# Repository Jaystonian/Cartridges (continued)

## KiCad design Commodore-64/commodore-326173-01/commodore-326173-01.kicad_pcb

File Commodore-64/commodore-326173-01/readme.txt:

Improved Commodore 326173-01 Cartridge

* Reset circuitry may be omitted completely

J1-J5 as expected for original Commodore PCB
  J1=~ROML~  J2=~ROMH~  J3=~GAME~  J4=~EXROM~  J5=Connect ~IO2~ to ~EXROM~

**U1 CONFIG**
U1=2364
  JP1-JP5 close arrowed "1" side
  JP6 close (R3,R4,R5 not needed)
  J7 not needed

U1=2764
  JP1-JP2 close "3" side
  JP3-JP5 close "1" side
  Install R4, R5
  J7 not needed

U1=27128 (two 8KB roms)
  JP1-JP3 close "3" side
  JP4-JP5 close "1" side
  Install R3, R4, R5
  J7 - SPST switch between Pin 1 & 2 (GND and SA13)

U1=27256 (four 8KB roms)
  JP1-JP4 close "3" side
  JP5 close "1" side
  Install R3, R4, R5

U1=27512 (eight 8KB roms)
  JP1-JP5 close "3" side
  Install R3, R4, R5

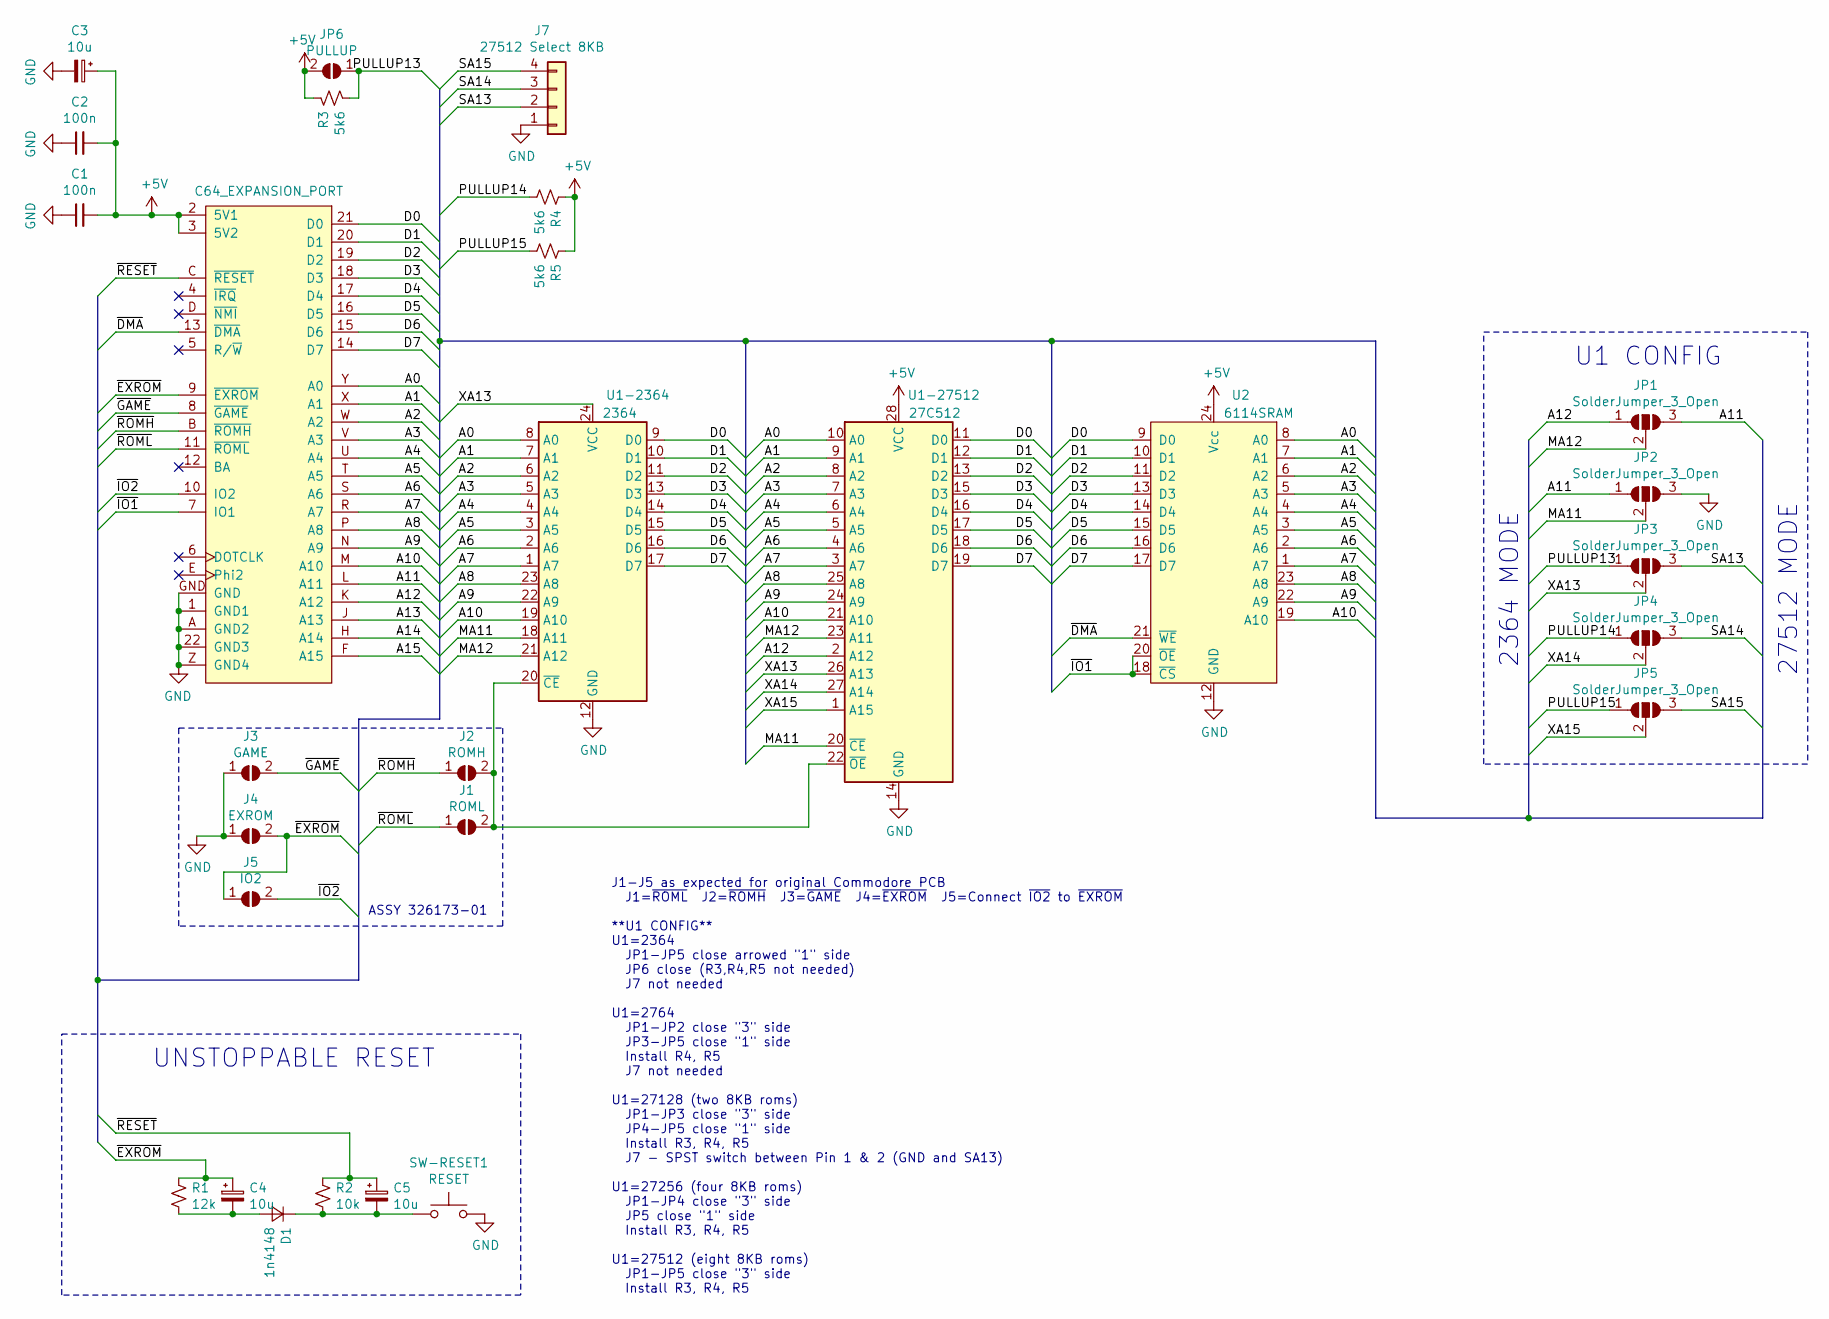
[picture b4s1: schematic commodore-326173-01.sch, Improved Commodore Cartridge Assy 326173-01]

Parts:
C1, C2: 100n; C_0805_2012Metric_Pad1.15x1.40mm_HandSolder
C3, C4, C5: 10u; CP_Radial_D5.0mm_P2.50mm
D1: 1n4148; D_DO-34_SOD68_P7.62mm_Horizontal
J1: ROML; SolderJumper-2_P1.3mm_Open_RoundedPad1.0x1.5mm
J2: ROMH; SolderJumper-2_P1.3mm_Open_RoundedPad1.0x1.5mm
J3: GAME; SolderJumper-2_P1.3mm_Open_RoundedPad1.0x1.5mm
J4: EXROM; SolderJumper-2_P1.3mm_Open_RoundedPad1.0x1.5mm
J5: IO2; SolderJumper-2_P1.3mm_Open_RoundedPad1.0x1.5mm
J7: 27512 Select 8KB; PinHeader_1x04_P2.54mm_Vertical
JP1, JP2, JP3, JP4, JP5: SolderJumper_3_Open; SolderJumper-3_P1.3mm_Open_RoundedPad1.0x1.5mm
JP6: PULLUP; SolderJumper-2_P1.3mm_Open_RoundedPad1.0x1.5mm
R1: 12k; R_0805_2012Metric_Pad1.15x1.40mm_HandSolder
R2: 10k; R_0805_2012Metric_Pad1.15x1.40mm_HandSolder
R3, R4, R5: 5k6; R_0805_2012Metric_Pad1.15x1.40mm_HandSolder
SW-RESET1: RESET; SW_PUSH_6mm_H8mm
U1-2364: 2364; DIP-24_W15.24mm
U1-27512: 27C512; DIP-28_W15.24mm
U2: 6114SRAM; DIP-24_W15.24mm
X1: C64_EXPANSION_PORT; C64_EXPANSION_CARD_68mm

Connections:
+5V: C1.2, C2.2, C3.1, JP6.2 (B), R3.1, R4.1, R5.1, U1-27512.28 (VCC), U2.24 (Vcc), X1.2 (5V1), X1.3 (5V2)
/A0: U1-2364.8 (A0), U1-27512.10 (A0), U2.8 (A0), X1.Y (A0)
/A1: U1-2364.7 (A1), U1-27512.9 (A1), U2.7 (A1), X1.X (A1)
/A2: U1-2364.6 (A2), U1-27512.8 (A2), U2.6 (A2), X1.W (A2)
/A3: U1-2364.5 (A3), U1-27512.7 (A3), U2.5 (A3), X1.V (A3)
/A4: U1-2364.4 (A4), U1-27512.6 (A4), U2.4 (A4), X1.U (A4)
/A5: U1-2364.3 (A5), U1-27512.5 (A5), U2.3 (A5), X1.T (A5)
/A6: U1-2364.2 (A6), U1-27512.4 (A6), U2.2 (A6), X1.S (A6)
/A7: U1-2364.1 (A7), U1-27512.3 (A7), U2.1 (A7), X1.R (A7)
/A8: U1-2364.23 (A8), U1-27512.25 (A8), U2.23 (A8), X1.P (A8)
/A9: U1-2364.22 (A9), U1-27512.24 (A9), U2.22 (A9), X1.N (A9)
/A10: U1-2364.19 (A10), U1-27512.21 (A10), U2.19 (A10), X1.M (A10)
/A11: JP1.3 (B), JP2.1 (A), X1.L (A11)
/A12: JP1.1 (A), U1-27512.2 (A12), X1.K (A12)
/A13: X1.J (A13)
/A14: X1.H (A14)
/A15: X1.F (A15)
/D0: U1-2364.9 (D0), U1-27512.11 (D0), U2.9 (D0), X1.21 (D0)
/D1: U1-2364.10 (D1), U1-27512.12 (D1), U2.10 (D1), X1.20 (D1)
/D2: U1-2364.11 (D2), U1-27512.13 (D2), U2.11 (D2), X1.19 (D2)
/D3: U1-2364.13 (D3), U1-27512.15 (D3), U2.13 (D3), X1.18 (D3)
/D4: U1-2364.14 (D4), U1-27512.16 (D4), U2.14 (D4), X1.17 (D4)
/D5: U1-2364.15 (D5), U1-27512.17 (D5), U2.15 (D5), X1.16 (D5)
/D6: U1-2364.16 (D6), U1-27512.18 (D6), U2.16 (D6), X1.15 (D6)
/D7: U1-2364.17 (D7), U1-27512.19 (D7), U2.17 (D7), X1.14 (D7)
/MA11: JP2.2 (C), U1-2364.18 (A11), U1-27512.20 (~CE)
/MA12: JP1.2 (C), U1-2364.21 (A12), U1-27512.23 (A11)
/PULLUP13: JP3.1 (A), JP6.1 (A), R3.2
/PULLUP14: JP4.1 (A), R4.2
/PULLUP15: JP5.1 (A), R5.2
/SA13: J7.2, JP3.3 (B)
/SA14: J7.3, JP4.3 (B)
/SA15: J7.4, JP5.3 (B)
/XA13: JP3.2 (C), U1-2364.24 (VCC), U1-27512.26 (A13)
/XA14: JP4.2 (C), U1-27512.27 (A14)
/XA15: JP5.2 (C), U1-27512.1 (A15)
/~DMA: U2.21 (~WE), X1.13 (~DMA~)
/~EXROM: C4.1, J4.2 (B), J5.1 (A), R1.2, X1.9 (~EXROM~)
/~GAME: J3.2 (B), X1.8 (~GAME~)
/~IO1: U2.18 (~CS), U2.20 (~OE), X1.7 (IO1)
/~IO2: J5.2 (B), X1.10 (IO2)
/~RESET: C5.1, R2.1, X1.C (~RESET~)
/~ROMH: J2.1 (A), X1.B (~ROMH~)
/~ROML: J1.1 (A), X1.11 (~ROML~)
GND: C1.1, C2.1, C3.2, J3.1 (A), J4.1 (A), J7.1, JP2.3 (B), SW-RESET1.2, U1-2364.12 (GND), U1-27512.14 (GND), U2.12 (GND), X1.1 (GND1), X1.22 (GND3), X1.A (GND2), X1.GND, X1.Z (GND4)
unnamed: C4.2, D1.2 (A), R1.1
unnamed: C5.2, D1.1 (K), R2.2, SW-RESET1.1
unnamed: J1.2 (B), J2.2 (B), U1-2364.20 (~CE), U1-27512.22 (~OE)

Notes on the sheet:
UNSTOPPABLE RESET
27512 MODE
2364 MODE
U1 CONFIG
ASSY 326173-01
J1-J5 as expected for original Commodore PCB J1=~ROML~ J2=~ROMH~ J3=~GAME~ J4=~EXROM~ J5=Connect ~IO2~ to ~EXROM~ **U1 CONFIG** U1=2364 JP1-JP5 close arrowed "1" side JP6 close (R3,R4,R5 not needed) J7 not needed U1=2764 JP1-JP2 close "3" side JP3-JP5 close "1" side Install R4, R5 J7 not needed U1=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

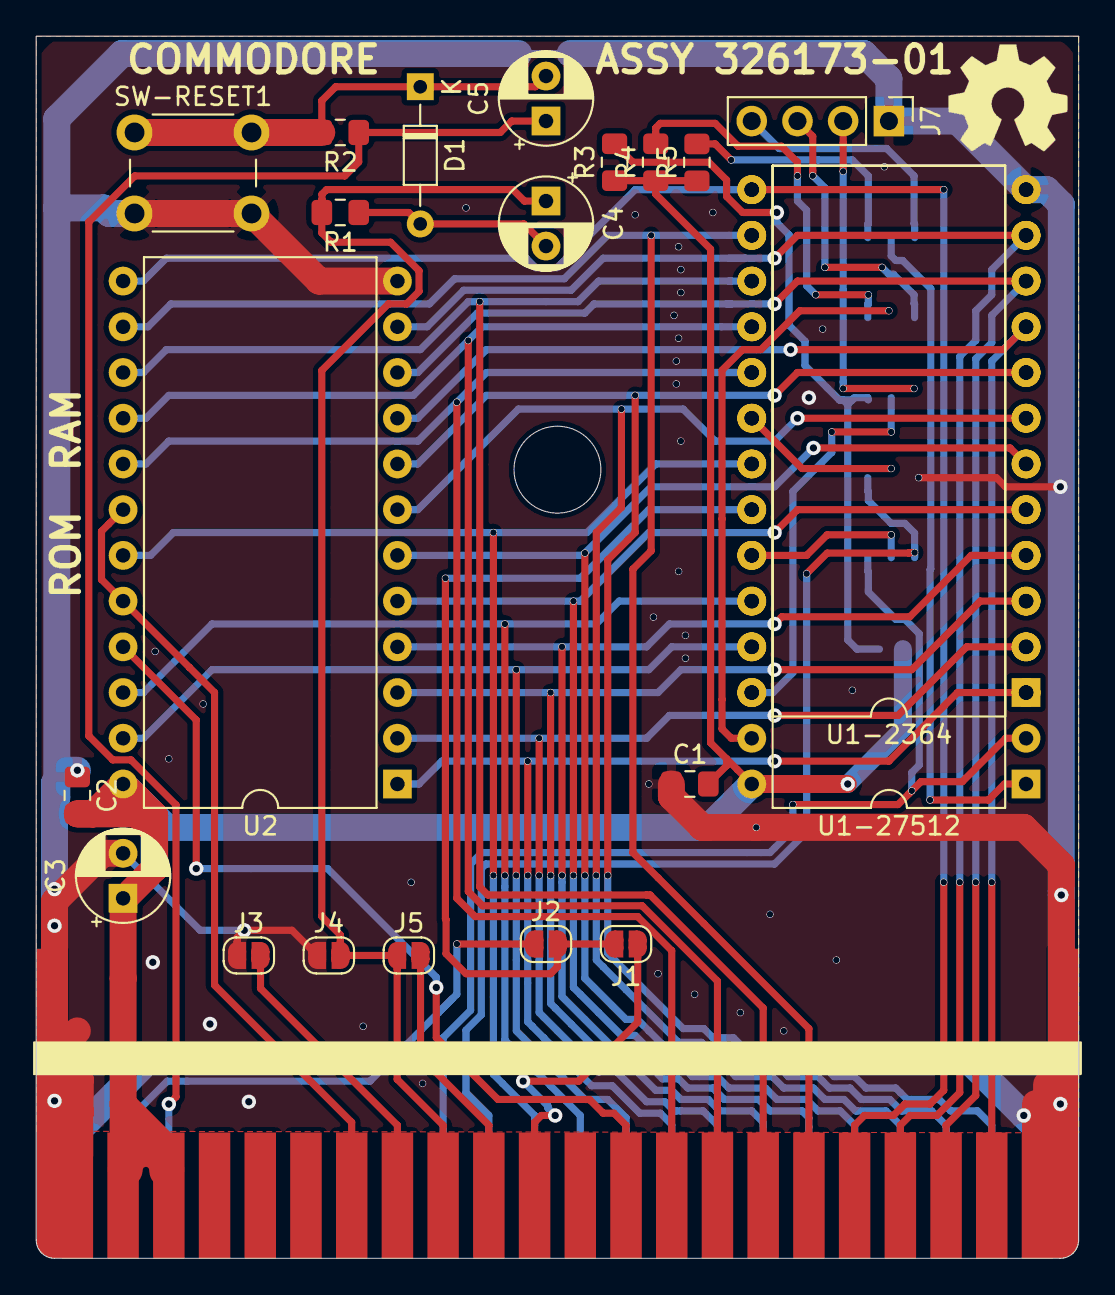
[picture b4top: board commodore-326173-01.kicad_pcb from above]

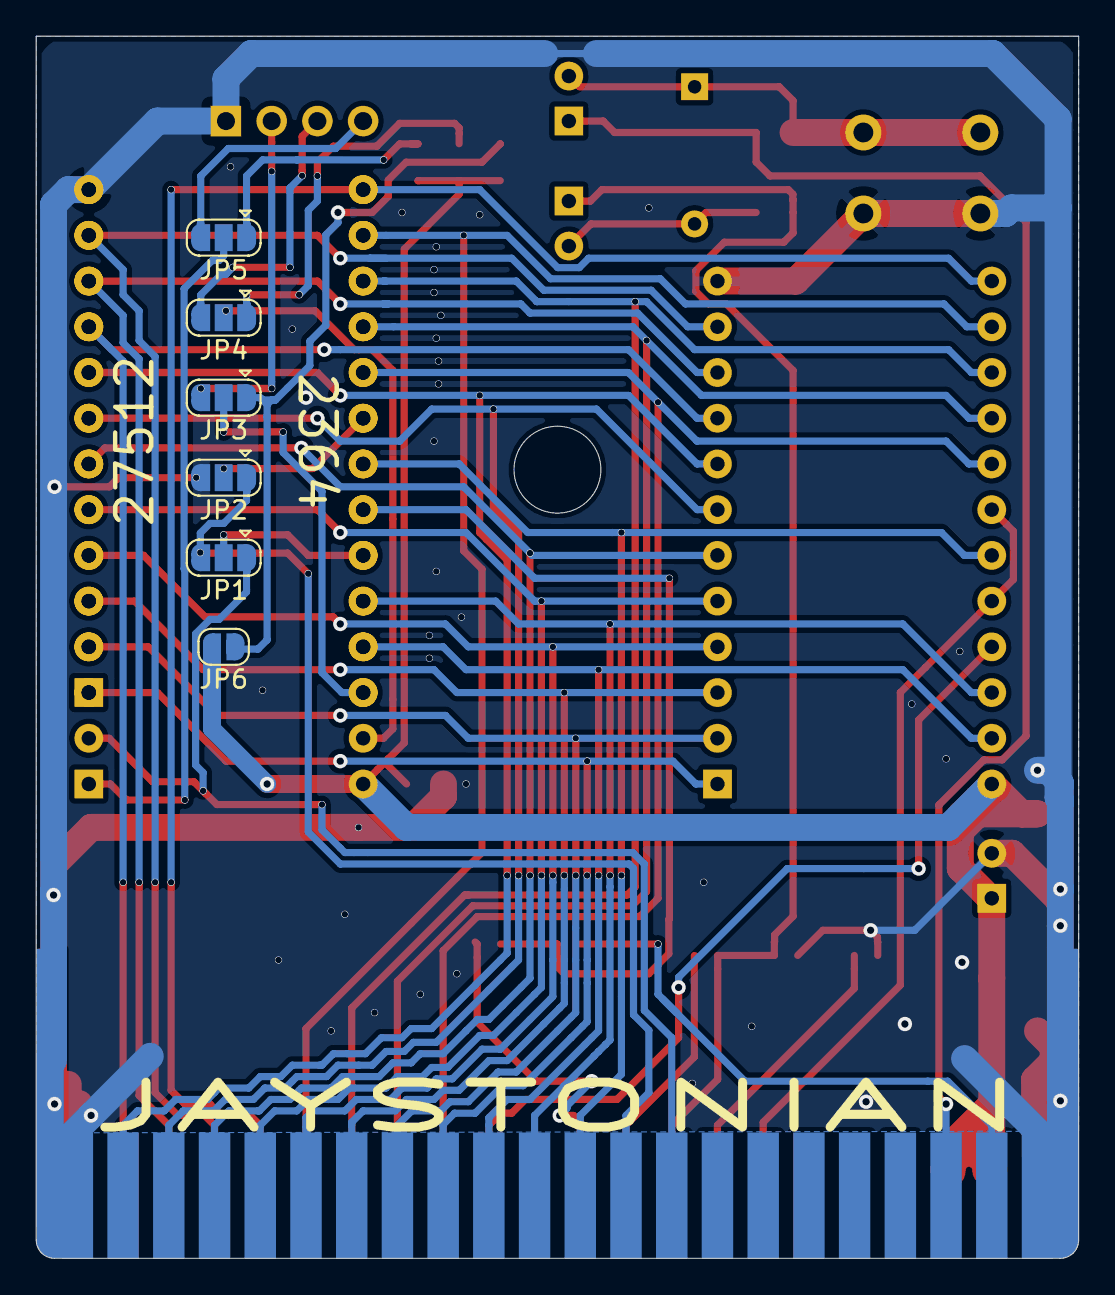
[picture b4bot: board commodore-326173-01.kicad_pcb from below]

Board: 2 copper layers, 57.9 x 67.9 mm, 28 parts (6 on the bottom side), 45 nets.

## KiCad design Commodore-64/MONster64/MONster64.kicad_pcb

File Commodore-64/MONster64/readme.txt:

MONster64 -- An STM32 Development Board for Commodore C64 & C128 Expansion Port

* Effectively an upgraded version of "Kung Fu Flash"

* fixes the PAL-only problem with KFF, due to jumper choice of DOTCLK or 
    standard 8MHz clock.  Internal PLL set to 468Mhz @ 8.000 MHz OSC_IN,
    which puts it close to 480MHz for NTSC and ~460MHz for PAL.

* may be installed with most other ARM-based code, such as BackBit, with light
    changes to GPIO.

* can be programmed with ST-LINK V2 or V3. I was unsuccessful connecting 
    a "blue pill" STM32F103 programmed to be an ST-LINK.

Contains an ARM Cortex M7 microcontroller, 22 exposed GPIO, 256MB Flash RAM, 
MicroSD card, MicroUSB -- all on a 2-LAYER PCB!

Also contains an expansion header for 10/100base-T networking or other 
high-speed interfacing such as video/sound.

Please see https://github.com/KimJorgensen/KungFuFlash for more information.

This project started when I took notice of KFF and started looking at STM32
schematics for all kinds of projects.  Then I decided I wanted an M7 based
card and not just an M4, and also on 2-layer PCB.

===============================================================================

2020-09-10: First status update. Beginning to port KFF code into CubeIDE.
  
    * Device is built, power domains are working, clock is working.

    * I can connect a MicroUSB cable to my computer, registers as a DFU, which
    can then be accessed by STM32 Cube Programmer via USB.
    
    * I can connect the ST-LINK V2 (SWDIO, SWCLK, GND, 5v, boot0 to link's 3v3)
    but it would not connect until I also connected 3v3 between the devices, 
    raising the target voltage reported in Cube Programmer from 3.17v to 3.20v.

    * I have updated the gerbers with small changes, I do not expect any further
    changes, device otherwise has passed basic tests.
===============================================================================

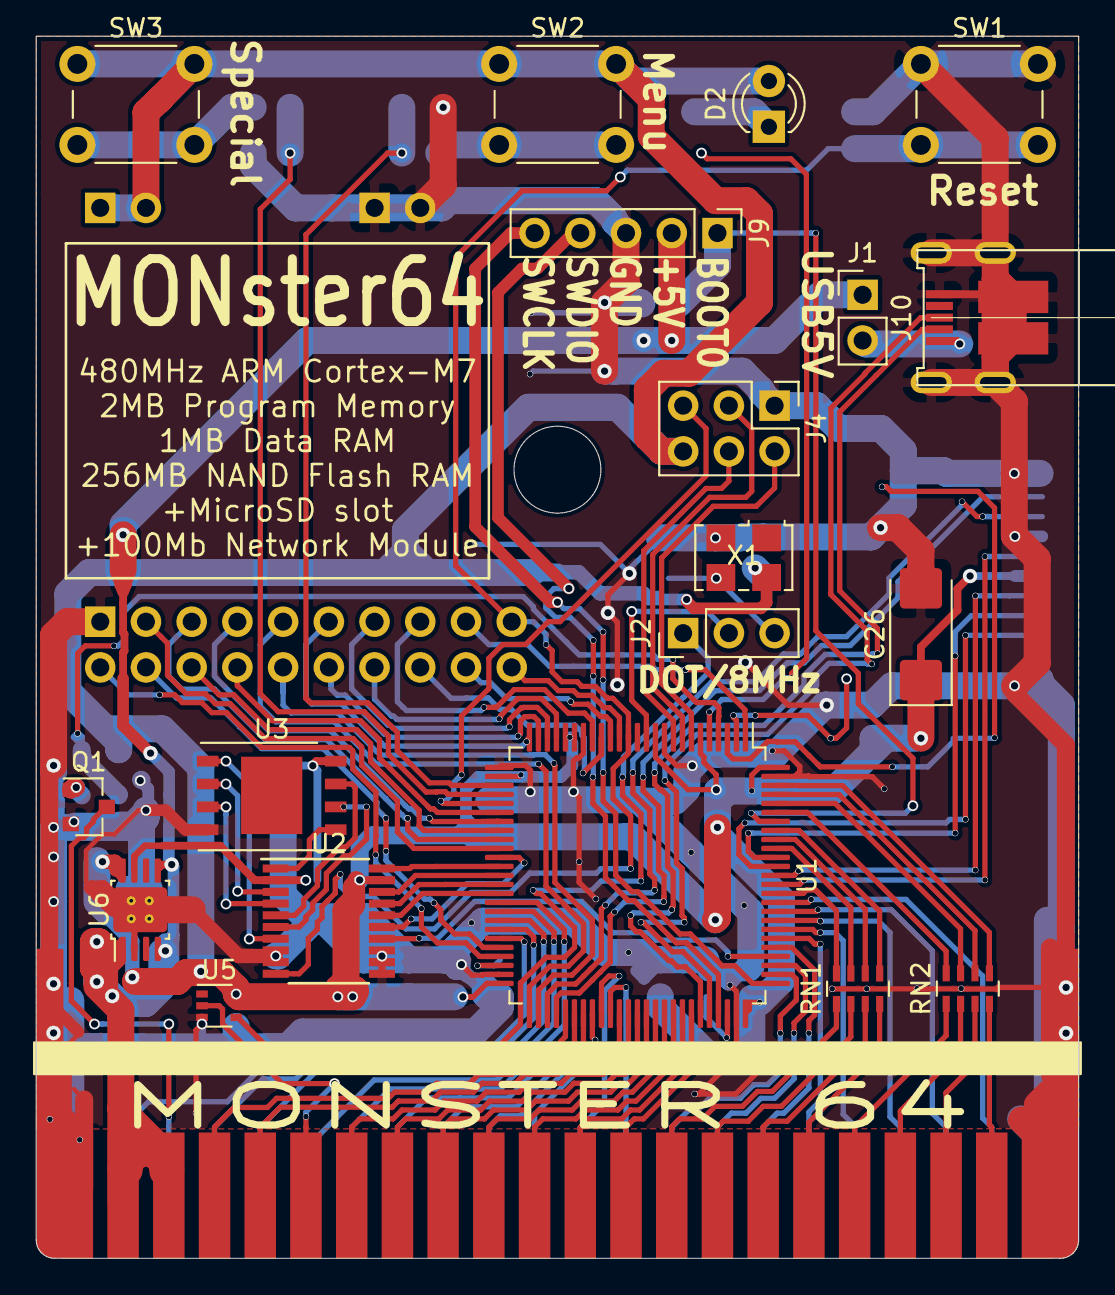
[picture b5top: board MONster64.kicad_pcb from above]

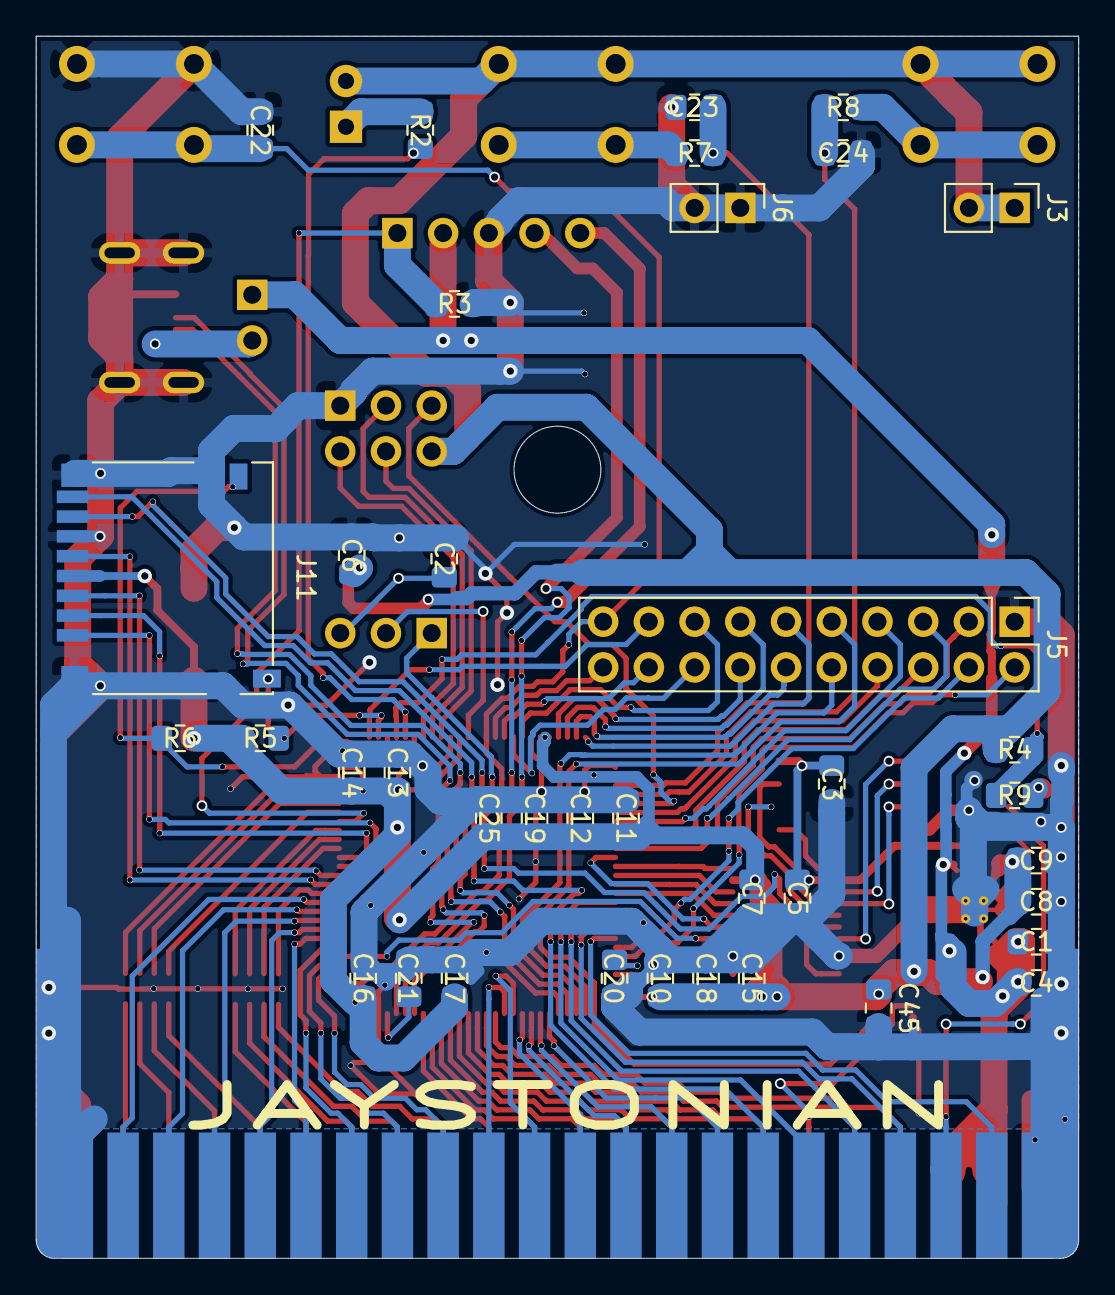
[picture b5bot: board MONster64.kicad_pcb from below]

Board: 2 copper layers, 57.9 x 67.9 mm, 58 parts (38 on the bottom side), 112 nets.

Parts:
C1, C9: 220n; C_0805_2012Metric_Pad1.15x1.40mm_HandSolder
C2: 18p; C_0805_2012Metric_Pad1.15x1.40mm_HandSolder
C3, C6: 10n; C_0805_2012Metric_Pad1.15x1.40mm_HandSolder
C4, C8: 10u; C_0805_2012Metric_Pad1.15x1.40mm_HandSolder
C5, C7, C11, C12, C13, C14, C15, C16, C17, C18, C19, C22, C23, C24, C25, C45: 100n; C_0805_2012Metric_Pad1.15x1.40mm_HandSolder
C10: 47n; C_0805_2012Metric_Pad1.15x1.40mm_HandSolder
C20, C21: 2u2 <100mOhm; C_0805_2012Metric_Pad1.15x1.40mm_HandSolder
C26: 22u; CP_EIA-6032-28_Kemet-C_Pad2.25x2.35mm_HandSolder
D2: LED; LED_D3.0mm_Clear
J1: USB Power; PinHeader_1x02_P2.54mm_Vertical
J2: CLOCK_JUMPER; PinHeader_1x03_P2.54mm_Vertical
J3: 3v3; PinHeader_1x02_P2.54mm_Vertical
J4: 4pin Expansion; PinHeader_2x03_P2.54mm_Vertical
J5: Conn_01x20; PinHeader_2x10_P2.54mm_Vertical
J6: GND; PinHeader_1x02_P2.54mm_Vertical
J9: SWD; PinHeader_1x05_P2.54mm_Vertical
J10: USB_B_Micro; USB_Micro-B_UJ2-MIBH-4
J11: Hirose_DM3D-SF; microSD_HC_Hirose_DM3D-SF
Q1: BC846BLT1G; SOT-23
R2, R7, R8, R9: 510R; R_0805_2012Metric_Pad1.15x1.40mm_HandSolder
R3, R4, R5, R6: 10k; R_0805_2012Metric_Pad1.15x1.40mm_HandSolder
RN1, RN2: 100R; R_Array_Concave_4x0603
SW1: Reset; SW_PUSH_6mm_H8mm
SW2: Menu; SW_PUSH_6mm_H8mm
SW3: Special; SW_PUSH_6mm_H8mm
U1: STM32H753VIT6; LQFP-100_14x14mm_P0.5mm
U2: TXS0108EQPWRQ1; TSSOP-20_4.4x6.5mm_P0.65mm
U3: W25M02GWZEIG; WSON-8_8x6mm
U5: SN74AUP1T34DCK; SOT-353_SC-70-5
U6: MIC5356-SGYMME; MSOP-8-1EP_3x3mm_P0.65mm_EP2.5x3mm_Mask1.73x2.36mm_ThermalV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
X1: DSC1001; Oscillator_SMD_SeikoEpson_SG8002LB-4Pin_5.0x3.2mm
XX1: C64_EXPANSION_PORT; C64_EXPANSION_CARD_68mm

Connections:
+1V8: C3.1, C5.1, U2.2, U3.8, U6.7
+3V3: C6.1, C7.1, C8.1, C9.1, C10.1, C11.1, C12.1, C13.1, C14.1, C15.1, C16.1, C17.1, C18.1, C19.1, C25.1, C26.1, C45.1, D2.2, J3.1, J3.2, J4.6, J11.4, R4.1, R5.2, R6.1, SW2.1, SW3.1, U1.6, U1.11, U1.20, U1.21, U1.27, U1.50, U1.75, U1.100, U2.19, U5.5, U6.8, X1.4
+5C: J1.2, J10.1
+5V: C1.1, C4.1, J1.1, J9.2, U6.1, U6.4, U6.5, XX1.2, XX1.3
/A0: U1.85, XX1.Y
/A1: U1.84, XX1.X
/A2: U1.83, XX1.W
/A3: U1.82, XX1.V
/A4: U1.81, XX1.U
/A5: U1.80, XX1.T
/A6: U1.78, XX1.S
/A7: U1.77, XX1.R
/A8: U1.60, XX1.P
/A9: U1.59, XX1.N
/A10: U1.58, XX1.M
/A11: U1.57, XX1.L
/A12: U1.56, XX1.K
/A13: U1.55, XX1.J
/A14: U1.41, XX1.H
/A15: U1.42, XX1.F
/BA: U1.68, XX1.12
/BOOT0: J9.1, R3.1, U1.94
/CD0: RN2.4, XX1.21
/CD1: RN2.3, XX1.20
/CD2: RN2.2, XX1.19
/CD3: RN2.1, XX1.18
/CD4: RN1.4, XX1.17
/CD5: RN1.3, XX1.16
/CD6: RN1.2, XX1.15
/CD7: RN1.1, XX1.14
/CLK8MHz: C2.2, J2.3, X1.3
/D0: RN2.5, U1.98
/D1: RN2.6, U1.97
/D2: RN2.7, U1.96
/D3: RN2.8, U1.95
/D4: RN1.5, U1.93
/D5: RN1.6, U1.92
/D6: RN1.7, U1.91
/D7: RN1.8, U1.86
/DOT: U5.2, XX1.6
/DOT_3v3: J2.1, U5.4
/ETH_COL: J5.11, U1.25
/ETH_CRS: J5.14, U1.22
/ETH_MDC: J5.18, U1.16
/ETH_MDIO: J5.12, U1.24
/ETH_RX_CLK: J5.13, U1.23
/ETH_RX_D0: J5.7, U1.32
/ETH_RX_D1: J5.6, U1.33
/ETH_RX_D2: J5.5, U1.34
/ETH_RX_D3: J5.3, U1.35
/ETH_RX_DV: J5.8, U1.31
/ETH_RX_ER: J5.4, U1.46
/ETH_TX_CLK: J5.15, U1.18
/ETH_TX_D0: J5.9, U1.51
/ETH_TX_D1: J5.10, U1.52
/ETH_TX_D2: J5.16, U1.17
/ETH_TX_D3: J5.17, U1.1
/ETH_TX_EN: J5.2, U1.47
/ETH_~INTPD: J5.20, U1.15
/MENU: C23.1, R7.2, U1.28
/NF_CLK: U1.36, U2.15
/NF_IO0: U1.37, U2.20
/NF_IO1: U1.38, U2.18
/NF_IO2: U1.39, U2.17
/NF_IO3: U1.40, U2.16
/NF_~CS: U1.79, U2.14
/PH0: J2.2, U1.12
/PHI2: U1.43, XX1.E
/R~W: U1.62, XX1.5
/SD_CK: J11.5, U1.87
/SD_CMD: J11.3, U1.88
/SD_D0: J11.7, U1.53
/SD_D1: J11.8, U1.54
/SD_D2: J11.1, U1.89
/SD_D3: J11.2, U1.90
/SD_DET1: J11.10, R5.1, U1.2
/SD_DET2: J11.9, R6.2, U1.3
/SPECIAL: C24.1, R8.2, U1.29
/SWCLK: J9.5, U1.76
/SWDIO: J9.4, U1.72
/USBB_DM: J10.2, U1.70
/USBB_DP: J10.3, U1.71
/XP1: J4.2, U1.7
/XP2: J4.3, U1.8
/XP3: J4.4, U1.9
/XP4: J4.5, U1.30
/~DMA: U1.69, XX1.13
/~EXROM: U1.65, XX1.9
/~GAME: U1.64, XX1.8
/~IO1: U1.63, XX1.7
/~IO2: U1.66, XX1.10
/~IRQ: U1.61, XX1.4
/~LED: R2.1, U1.5
/~NMI: U1.44, XX1.D
/~RESET: Q1.3, XX1.C
/~ROMH: U1.45, XX1.B
/~ROML: U1.67, XX1.11
/~RST: C22.1, J5.19, SW1.2, U1.14, U2.10
/~RST_O: R4.2, R9.2, U1.4
GND: C1.2, C2.1, C3.2, C4.2, C5.2, C6.2, C7.2, C8.2, C9.2, C10.2, C11.2, C12.2, C13.2, C14.2, C15.2, C16.2, C17.2, C18.2, C19.2, C20.2, C21.2, C22.2, C23.2, C24.2, C25.2, C26.2, C45.2, J4.1, J5.1, J6.1, J6.2, J9.3, J10.5, J10.6, J11.6, J11.11, Q1.2, R3.2, SW1.1, U1.10, U1.19, U1.26, U1.49, U1.74, U1.99, U2.8, U2.9, U2.11, U2.12, U2.13, U3.4, U5.3, U6.2, U6.9, X1.2, XX1.1, XX1.22, XX1.A, XX1.Z
unnamed: C20.1, U1.48
unnamed: C21.1, U1.73
unnamed: D2.1, R2.2
unnamed: Q1.1, R9.1
unnamed: R7.1, SW2.2
unnamed: R8.1, SW3.2
unnamed: U2.1, U3.5
unnamed: U2.3, U3.2
unnamed: U2.4, U3.3
unnamed: U2.5, U3.7
unnamed: U2.6, U3.6
unnamed: U2.7, U3.1

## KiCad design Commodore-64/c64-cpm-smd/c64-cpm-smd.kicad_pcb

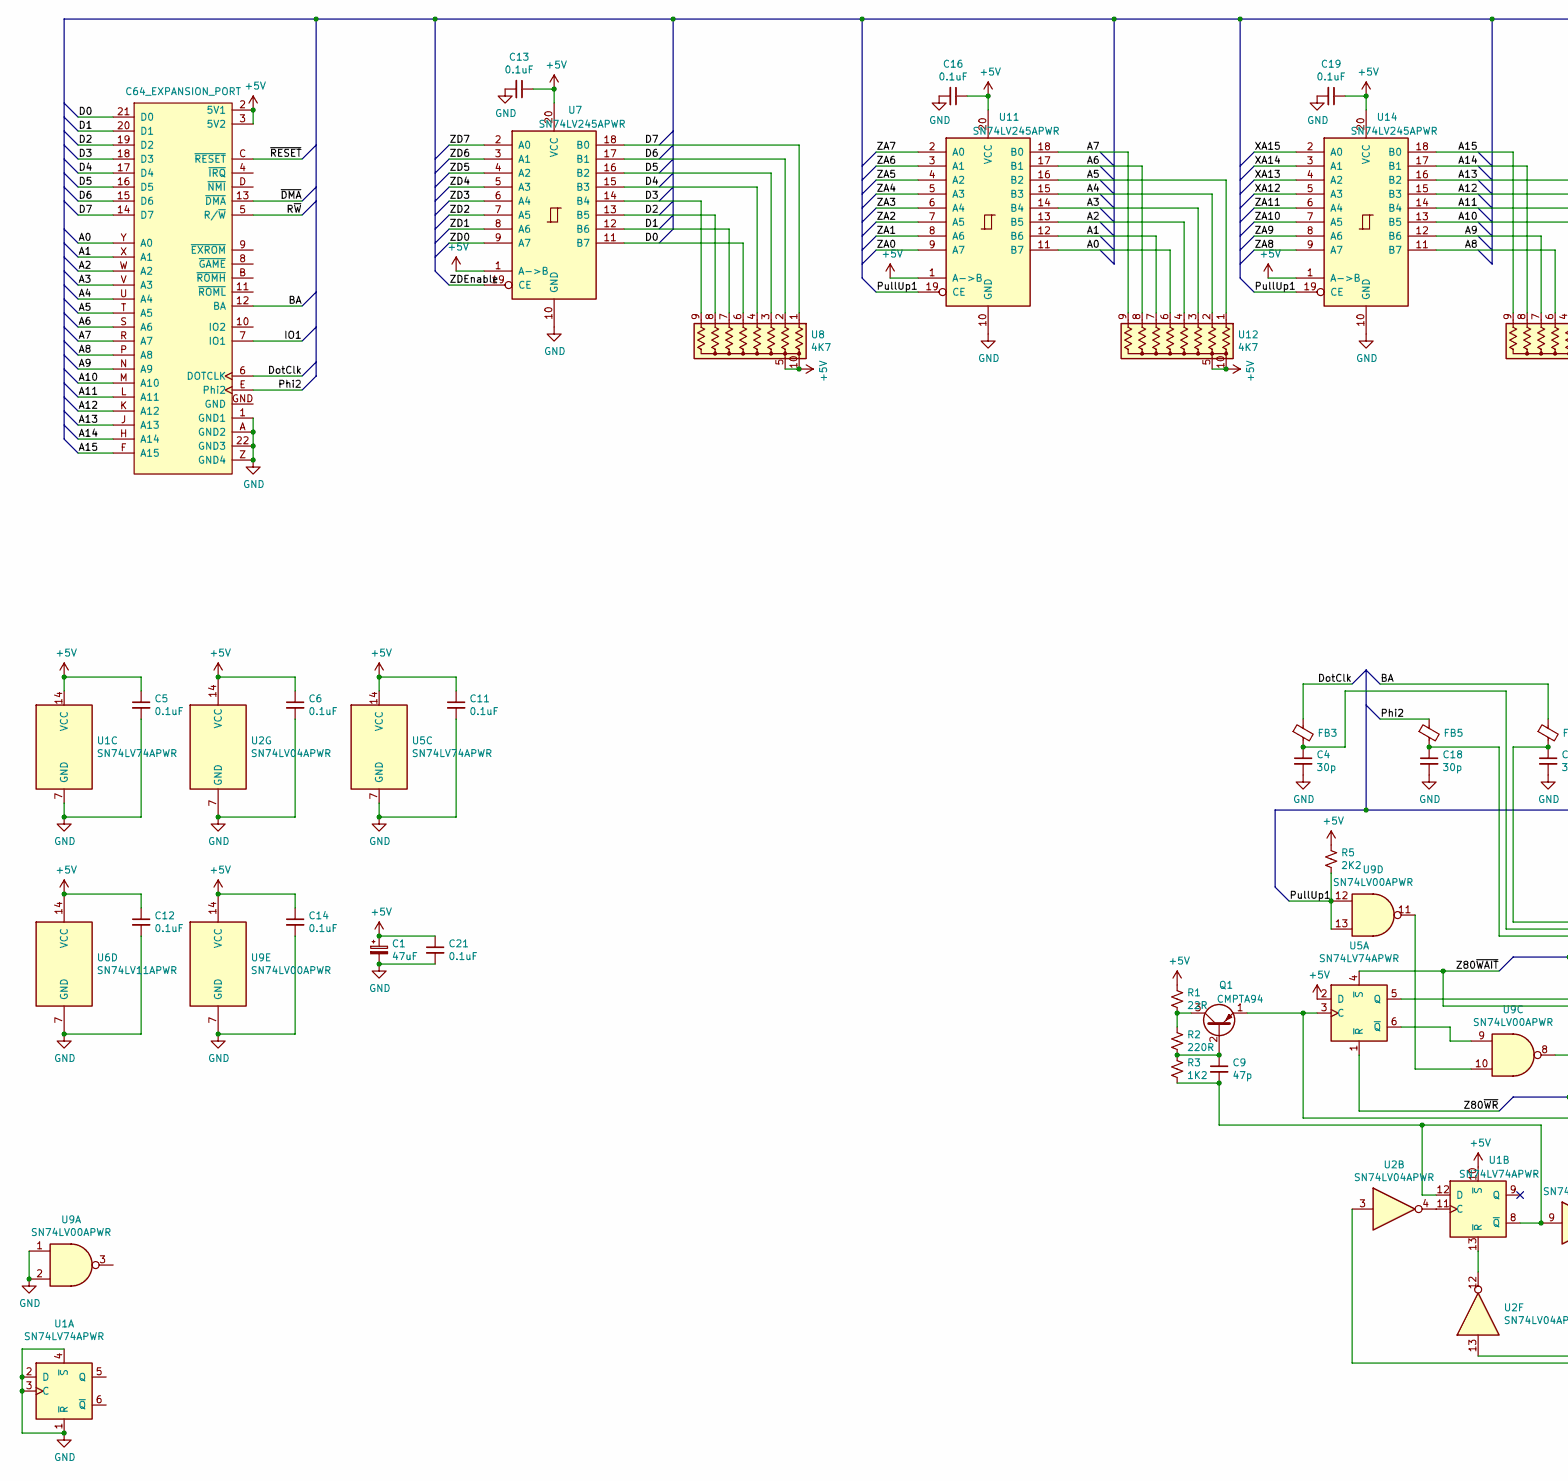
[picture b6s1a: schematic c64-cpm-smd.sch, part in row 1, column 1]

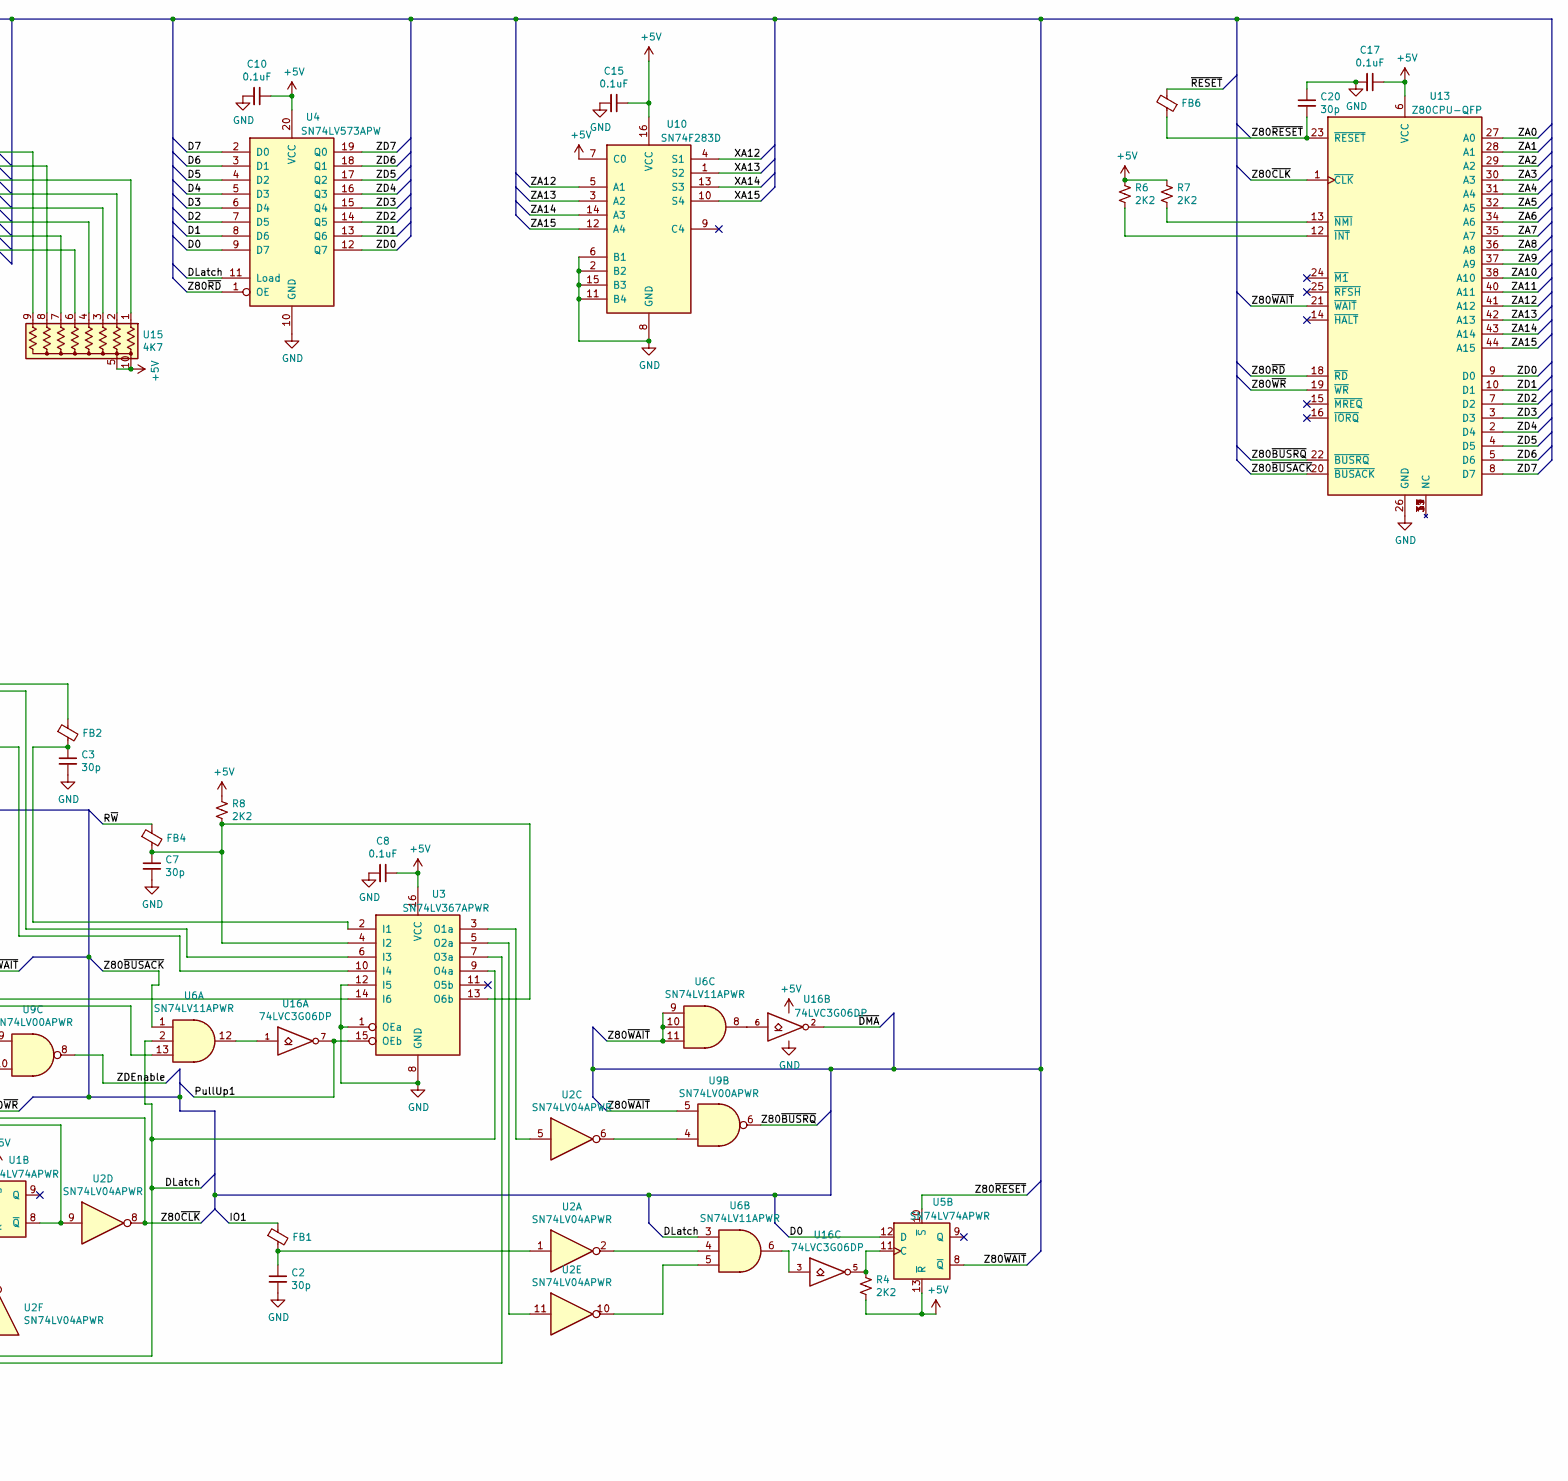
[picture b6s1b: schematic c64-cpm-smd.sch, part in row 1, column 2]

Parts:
C1: 47uF; CP_Radial_D6.3mm_P2.50mm
C2, C3, C4, C7, C18, C20: 30p; C_0805_2012Metric_Pad1.15x1.40mm_HandSolder
C5, C6, C8, C10, C11, C12, C13, C14, C15, C16, C17, C19, C21: 0.1uF; C_0805_2012Metric_Pad1.15x1.40mm_HandSolder
C9: 47p; C_0805_2012Metric_Pad1.15x1.40mm_HandSolder
FB1, FB2, FB3, FB4, FB5, FB6: 2508052027Z0; R_0805_2012Metric_Pad1.15x1.40mm_HandSolder
Q1: CMPTA94; SOT-23
R1: 22R; R_0805_2012Metric_Pad1.15x1.40mm_HandSolder
R2: 220R; R_0805_2012Metric_Pad1.15x1.40mm_HandSolder
R3: 1K2; R_0805_2012Metric_Pad1.15x1.40mm_HandSolder
R4, R5, R6, R7, R8: 2K2; R_0805_2012Metric_Pad1.15x1.40mm_HandSolder
U1, U5: SN74LV74APWR; TSSOP-14_4.4x5mm_P0.65mm
U2: SN74LV04APWR; TSSOP-14_4.4x5mm_P0.65mm
U3: SN74LV367APWR; TSSOP-16_4.4x5mm_P0.65mm
U4: SN74LV573APW; TSSOP-20_4.4x6.5mm_P0.65mm
U6: SN74LV11APWR; TSSOP-14_4.4x5mm_P0.65mm
U7, U11, U14: SN74LV245APWR; TSSOP-20_4.4x6.5mm_P0.65mm
U8, U12, U15: 4K7; R_Array_Convex_5x1206
U9: SN74LV00APWR; TSSOP-14_4.4x5mm_P0.65mm
U10: SN74F283D; SOIC-16_3.9x9.9mm_P1.27mm
U13: Z80CPU-QFP; LQFP-44_10x10mm_P0.8mm
U16: 74LVC3G06DP; TSSOP-8_3x3mm_P0.65mm
X1: C64_EXPANSION_PORT; C64_EXPANSION_CARD_49mm

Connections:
+5V: C1.1, C5.1, C6.1, C8.1, C10.1, C11.1, C12.1, C13.1, C14.1, C15.1, C16.1, C17.1, C19.1, C21.1, R1.1, R4.2, R5.1, R6.1, R7.1, R8.1, U1.10 (~S), U1.14 (VCC), U2.14 (VCC), U3.16 (VCC), U4.20 (VCC), U5.2 (D), U5.13 (~R), U5.14 (VCC), U6.14 (VCC), U7.1 (A->B), U7.20 (VCC), U8.5 (common), U8.10 (common), U9.14 (VCC), U10.7 (C0), U10.16 (VCC), U11.1 (A->B), U11.20 (VCC), U12.5 (common), U12.10 (common), U13.6 (VCC), U14.1 (A->B), U14.20 (VCC), U15.5 (common), U15.10 (common), U16.8 (VCC), X1.2 (5V1), X1.3 (5V2)
/A0: U11.11 (B7), U12.6 (R5), X1.Y (A0)
/A1: U11.12 (B6), U12.7 (R6), X1.X (A1)
/A2: U11.13 (B5), U12.4 (R4), X1.W (A2)
/A3: U11.14 (B4), U12.3 (R3), X1.V (A3)
/A4: U11.15 (B3), U12.2 (R2), X1.U (A4)
/A5: U11.16 (B2), U12.1 (R1), X1.T (A5)
/A6: U11.17 (B1), U12.8 (R7), X1.S (A6)
/A7: U11.18 (B0), U12.9 (R8), X1.R (A7)
/A8: U14.11 (B7), U15.6 (R5), X1.P (A8)
/A9: U14.12 (B6), U15.7 (R6), X1.N (A9)
/A10: U14.13 (B5), U15.4 (R4), X1.M (A10)
/A11: U14.14 (B4), U15.3 (R3), X1.L (A11)
/A12: U14.15 (B3), U15.2 (R2), X1.K (A12)
/A13: U14.16 (B2), U15.1 (R1), X1.J (A13)
/A14: U14.17 (B1), U15.8 (R7), X1.H (A14)
/A15: U14.18 (B0), U15.9 (R8), X1.F (A15)
/BA: FB2.1, X1.12 (BA)
/D0: U4.9 (D7), U5.12 (D), U7.11 (B7), U8.6 (R5), X1.21 (D0)
/D1: U4.8 (D6), U7.12 (B6), U8.7 (R6), X1.20 (D1)
/D2: U4.7 (D5), U7.13 (B5), U8.8 (R7), X1.19 (D2)
/D3: U4.6 (D4), U7.14 (B4), U8.9 (R8), X1.18 (D3)
/D4: U4.5 (D3), U7.15 (B3), U8.4 (R4), X1.17 (D4)
/D5: U4.4 (D2), U7.16 (B2), U8.3 (R3), X1.16 (D5)
/D6: U4.3 (D1), U7.17 (B1), U8.2 (R2), X1.15 (D6)
/D7: U4.2 (D0), U7.18 (B0), U8.1 (R1), X1.14 (D7)
/DLatch: U2.13, U3.9 (O4a), U4.11 (Load), U6.2, U6.3
/DotClk: FB3.1, X1.6 (DOTCLK)
/IO1: FB1.1, X1.7 (IO1)
/Phi2: FB5.1, X1.E (Phi2)
/PullUp1: R5.2, U3.15 (OEb), U9.12, U9.13, U11.19 (CE), U14.19 (CE), U16.7
/R~W: FB4.1, X1.5 (R/~W~)
/XA12: U10.4 (S1), U14.5 (A3)
/XA13: U10.1 (S2), U14.4 (A2)
/XA14: U10.13 (S3), U14.3 (A1)
/XA15: U10.10 (S4), U14.2 (A0)
/Z80~BUSACK: U6.1, U13.20 (~BUSACK~)
/Z80~BUSRQ: U9.6, U13.22 (~BUSRQ~)
/Z80~CLK: Q1.1 (E), U2.8, U5.3 (C), U13.1 (~CLK~)
/Z80~RD: U4.1 (OE), U13.18 (~RD~)
/Z80~RESET: C20.2, FB6.1, U5.10 (~S), U13.23 (~RESET~)
/Z80~WAIT: U5.4 (~S), U5.8 (~Q), U6.9, U6.10, U6.11, U6.13, U9.5, U13.21 (~WAIT~)
/Z80~WR: U5.1 (~R), U13.19 (~WR~)
/ZA0: U11.9 (A7), U13.27 (A0)
/ZA1: U11.8 (A6), U13.28 (A1)
/ZA2: U11.7 (A5), U13.29 (A2)
/ZA3: U11.6 (A4), U13.30 (A3)
/ZA4: U11.5 (A3), U13.31 (A4)
/ZA5: U11.4 (A2), U13.32 (A5)
/ZA6: U11.3 (A1), U13.34 (A6)
/ZA7: U11.2 (A0), U13.35 (A7)
/ZA8: U13.36 (A8), U14.9 (A7)
/ZA9: U13.37 (A9), U14.8 (A6)
/ZA10: U13.38 (A10), U14.7 (A5)
/ZA11: U13.40 (A11), U14.6 (A4)
/ZA12: U10.5 (A1), U13.41 (A12)
/ZA13: U10.3 (A2), U13.42 (A13)
/ZA14: U10.14 (A3), U13.43 (A14)
/ZA15: U10.12 (A4), U13.44 (A15)
/ZD0: U4.12 (Q7), U7.9 (A7), U13.9 (D0)
/ZD1: U4.13 (Q6), U7.8 (A6), U13.10 (D1)
/ZD2: U4.14 (Q5), U7.7 (A5), U13.7 (D2)
/ZD3: U4.15 (Q4), U7.6 (A4), U13.3 (D3)
/ZD4: U4.16 (Q3), U7.5 (A3), U13.2 (D4)
/ZD5: U4.17 (Q2), U7.4 (A2), U13.4 (D5)
/ZD6: U4.18 (Q1), U7.3 (A1), U13.5 (D6)
/ZD7: U4.19 (Q0), U7.2 (A0), U13.8 (D7)
/ZDEnable: U7.19 (CE), U9.8
/~DMA: U16.2, X1.13 (~DMA~)
/~RESET: FB6.2, X1.C (~RESET~)
GND: C1.2, C2.2, C3.2, C4.2, C5.2, C6.2, C7.2, C8.2, C10.2, C11.2, C12.2, C13.2, C14.2, C15.2, C16.2, C17.2, C18.2, C19.2, C20.1, C21.2, U1.1 (~R), U1.2 (D), U1.3 (C), U1.4 (~S), U1.7 (GND), U2.7 (GND), U3.1 (OEa), U3.8 (GND), U3.12 (I5), U4.10 (GND), U5.7 (GND), U6.7 (GND), U7.10 (GND), U9.1, U9.2, U9.7 (GND), U10.2 (B2), U10.6 (B1), U10.8 (GND), U10.11 (B4), U10.15 (B3), U11.10 (GND), U13.26 (GND), U14.10 (GND), U16.4 (GND), X1.1 (GND1), X1.22 (GND3), X1.A (GND2), X1.Z (GND4)
unnamed: C2.1, FB1.2, U2.1
unnamed: C3.1, FB2.2, U3.2 (I1)
unnamed: C4.1, FB3.2, U3.6 (I3)
unnamed: C7.1, FB4.2, R8.2, U3.4 (I2), U3.13 (O6b)
unnamed: C9.1, Q1.2 (B), R2.2, R3.1
unnamed: C9.2, R3.2, U1.8 (~Q), U1.12 (D), U2.9
unnamed: C18.1, FB5.2, U3.10 (I4)
unnamed: Q1.3 (C), R1.2, R2.1
unnamed: R4.1, U5.11 (C), U16.5
unnamed: R6.2, U13.12 (~INT~)
unnamed: R7.2, U13.13 (~NMI~)
unnamed: U1.11 (C), U2.4
unnamed: U1.13 (~R), U2.12
unnamed: U2.2, U6.4
unnamed: U2.3, U3.7 (O3a)
unnamed: U2.5, U3.3 (O1a)
unnamed: U2.6, U9.4
unnamed: U2.10, U6.5
unnamed: U2.11, U3.5 (O2a)
unnamed: U3.14 (I6), U5.5 (Q)
unnamed: U5.6 (~Q), U9.9
unnamed: U9.10, U9.11
unnamed: U13.11 (NC), U13.17 (NC), U13.33 (NC), U13.39 (NC)
unnamed: U6.12, U16.1
unnamed: U6.6, U16.3
unnamed: U6.8, U16.6
